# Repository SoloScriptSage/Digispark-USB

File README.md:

# ⚡ Digispark USB Development Board

A custom PCB clone of the Digispark development board — a minimal ATtiny85-based microcontroller board with native USB programming support. Designed from scratch in KiCad.

---

## What Is This

The original Digispark is a tiny Arduino-compatible board built around the ATtiny85. This is a custom PCB recreation of that design, including the USB low-speed interface circuit for programming directly over USB without a separate programmer.

The board breaks out all available ATtiny85 GPIO pins to two 4-pin headers for connecting peripherals.

---

## Circuit Overview

```
[USB Connector] → [USB Protection Circuit] → [ATtiny85] → [GPIO Headers]
```

**ATtiny85 Microcontroller**
8-pin AVR MCU running at up to 16.5 MHz (internal PLL clock when using Micronucleus bootloader). 6 usable GPIO pins (PB0–PB5), supports I2C, SPI, PWM, and ADC.

**USB Interface**
USB low-speed (1.5 Mbps) is bit-banged in software by the Micronucleus bootloader. The hardware side requires:
- Two 68Ω series resistors on D+ and D− lines (impedance matching)
- Two 3.6V Zener diodes (D1, D2) clamping the data lines to USB-safe voltage levels
- 1.5kΩ pull-up resistor (R4) on D+ to signal low-speed device to the host

**Decoupling**
100nF capacitor (C1) on the VCC pin filters supply noise close to the MCU.

**GPIO Headers**
J1 and J2 break out all ATtiny85 pins for connecting sensors, displays, or other peripherals.

---

## Pinout

| Pin | ATtiny85 | Function |
|-----|----------|----------|
| PB0 | Pin 5 | GPIO / PWM / AREF |
| PB1 | Pin 6 | GPIO / PWM |
| PB2 | Pin 7 | GPIO / I2C SDA / ADC1 |
| PB3 | Pin 2 | GPIO / ADC3 |
| PB4 | Pin 3 | GPIO / ADC2 |
| PB5 | Pin 1 | GPIO / RESET |

---

## Schematic

Designed in **KiCad 9.0.2**. Full schematic and PCB layout files included in the repository.

---

## Programming

Flash using the [Micronucleus bootloader](https://github.com/micronucleus/micronucleus) over USB, or use any AVR ISP programmer via the RESET/SPI pins on the header.

Compatible with Arduino IDE using the [Digistump ATtiny85 board package](https://github.com/digistump/DigistumpArduino).

---

## What I Learned

- USB low-speed electrical interface design (D+/D− termination, Zener clamping)
- ATtiny85 minimal circuit requirements
- PCB design for USB-connected embedded hardware in KiCad
- Impedance-sensitive routing for USB data lines

---

## Author

**Vladyslav Hirchuk** — [GitHub](https://github.com/SoloScriptSage) · [LinkedIn](https://linkedin.com/in/vladyslavhirchuk)

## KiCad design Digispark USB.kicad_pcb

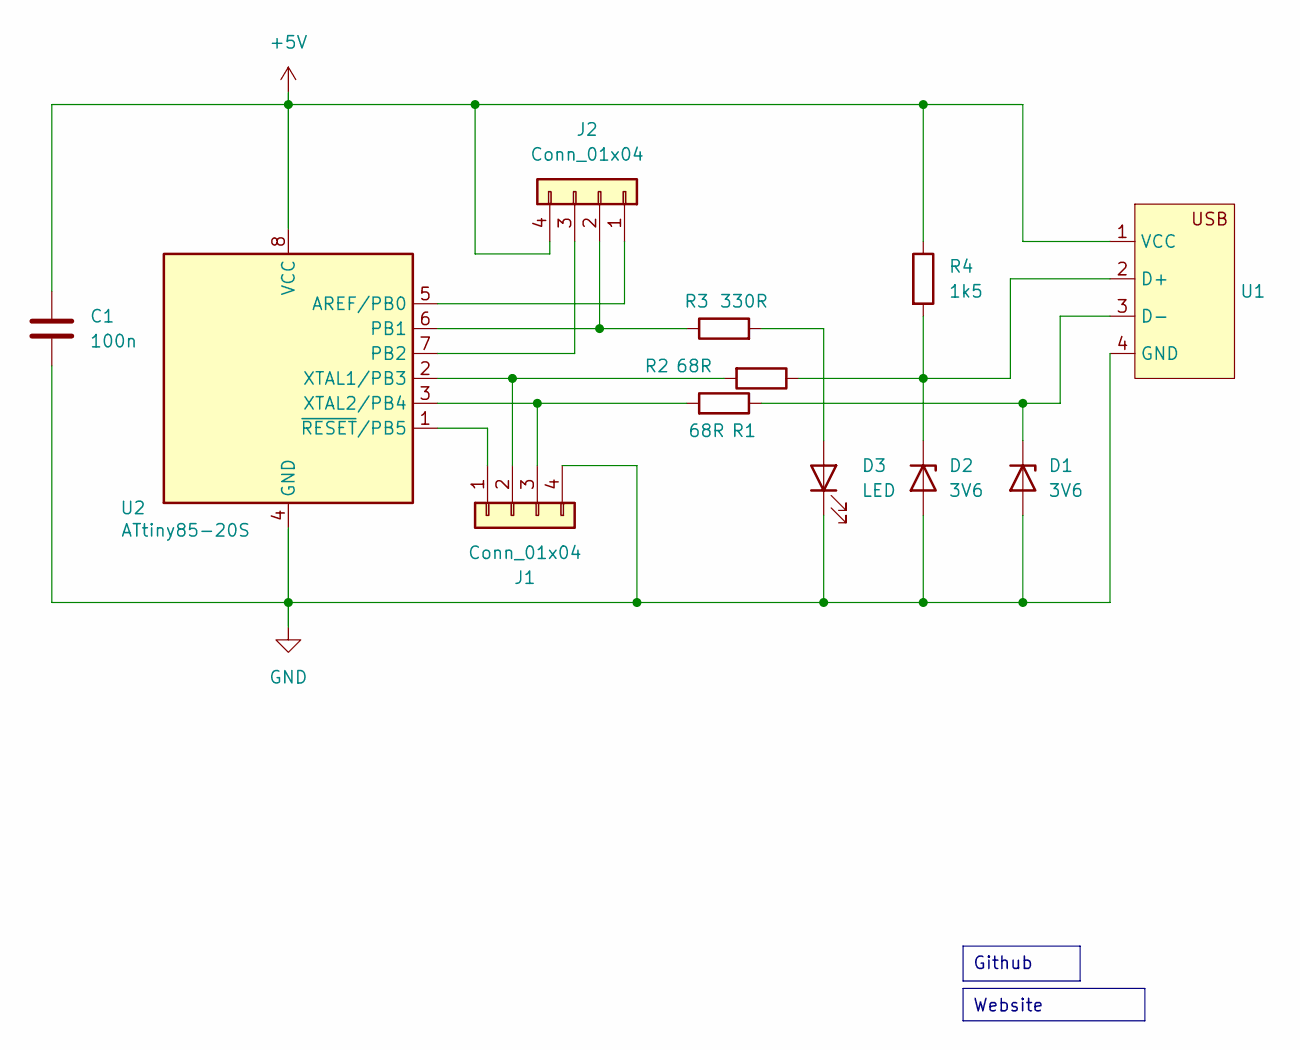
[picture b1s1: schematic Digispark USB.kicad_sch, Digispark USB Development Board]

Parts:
C1: 100n; C_1206_3216Metric_Pad1.33x1.80mm_HandSolder
D1, D2: 3V6; D_SOD-123
D3: LED; LED_D3.0mm
J1, J2: Conn_01x04; PinHeader_1x04_P2.54mm_Vertical
R1, R2: 68R; R_0805_2012Metric_Pad1.20x1.40mm_HandSolder
R3: 330R; R_0805_2012Metric_Pad1.20x1.40mm_HandSolder
R4: 1k5; R_0805_2012Metric_Pad1.20x1.40mm_HandSolder
U1: PCB_USB_Connector
U2: ATtiny85-20S; SOIC-8_5.3x5.3mm_P1.27mm

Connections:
+5V: C1.1, J2.4, R4.1, U1.1 (VCC), U2.8 (VCC)
GND: C1.2, D1.2 (A), D2.2 (A), D3.1 (K), J1.4, U1.4 (GND), U2.4 (GND)
unnamed: D1.1 (K), R1.1, U1.3 (D-)
unnamed: D2.1 (K), R2.1, R4.2, U1.2 (D+)
unnamed: D3.2 (A), R3.2
unnamed: J1.1, U2.1 (~RESET/PB5)
unnamed: J1.2, R2.2, U2.2 (XTAL1/PB3)
unnamed: J1.3, R1.2, U2.3 (XTAL2/PB4)
unnamed: J2.1, U2.5 (AREF/PB0)
unnamed: J2.2, R3.1, U2.6 (PB1)
unnamed: J2.3, U2.7 (PB2)

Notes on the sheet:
Website
Github

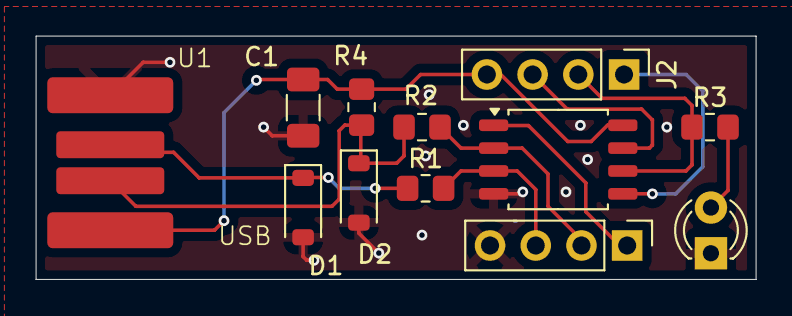
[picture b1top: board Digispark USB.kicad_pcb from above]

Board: 2 copper layers, 40.0 x 13.5 mm, 12 parts (0 on the bottom side), 11 nets.

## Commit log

2025-11-07 Initial Commit:
2025-11-07 pdfs
2025-11-09 Sctructurized a little bit:
2026-03-05 Update PCB layout, remove panel files, add gitignore for backups
2026-03-05 Add README and PCB image
2026-03-05 Remove backups and temp files, fix gitignore
